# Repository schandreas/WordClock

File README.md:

# WordClock
WordClock based on a cheap stm32 chip (STM32F030RCT6TR)

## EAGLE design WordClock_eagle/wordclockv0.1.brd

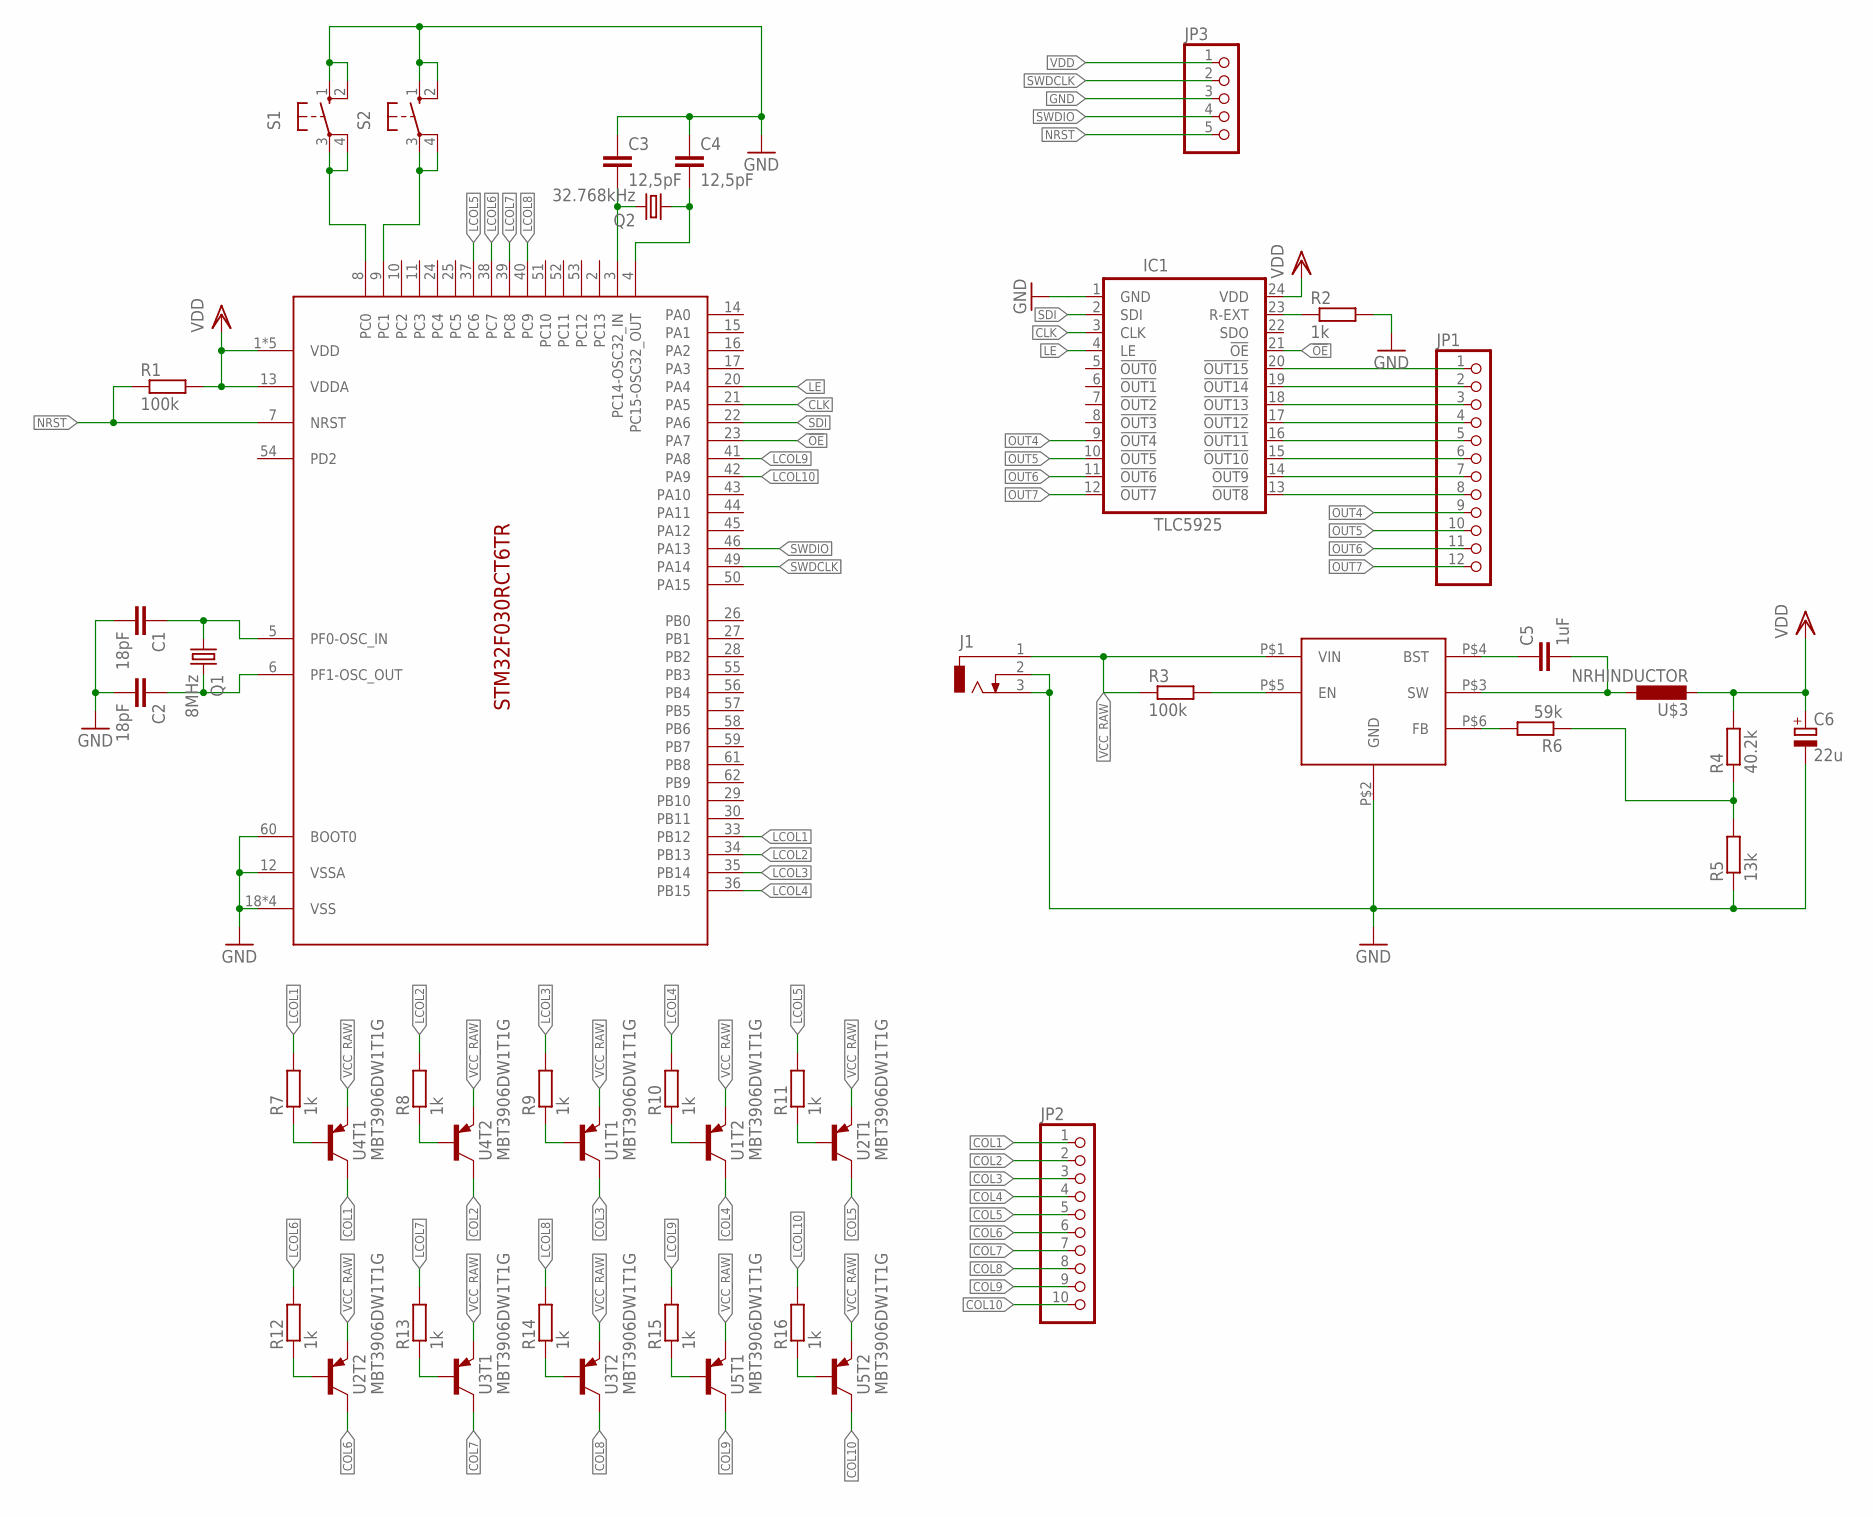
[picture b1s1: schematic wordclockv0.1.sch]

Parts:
C1, C2: 18pF; C0402
C3, C4: 12,5pF; C0402
C5: 1uF; C0805
C6: 22u; 153CLV-0405
IC1: TLC5925; SO24W
J1: DCJ0303
JP1: PINHD-1X12; 1X12
JP2: PINHD-1X10; 1X10
JP3: PINHD-1X5; 1X05
Q1: 8MHz; HC49U-V
Q2: 32.768kHz; TC26V
R1, R3: 100k; M1206
R2, R7, R8, R9, R10, R11, R12, R13, R14, R15, R16: 1k; M1206
R4: 40.2k; M1206
R5: 13k; M1206
R6: 59k; M1206
S1, S2: 10-XX; B3F-10XX
U1, U2, U3, U4, U5: MBT3906DW1T1G; SOT363-INFINION
U$1: STM32F030RCT6TRLQFP64; LQFP64
U$2: AP65111A; TSOT26
U$3: NRHINDUCTOR

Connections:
!OE: IC1.21 (!OE), U$1.23 (PA7)
CLK: IC1.3 (CLK), U$1.21 (PA5)
COL1: JP2.1, U4.6 (C)
COL2: JP2.2, U4.3 (C)
COL3: JP2.3, U1.6 (C)
COL4: JP2.4, U1.3 (C)
COL5: JP2.5, U2.6 (C)
COL6: JP2.6, U2.3 (C)
COL7: JP2.7, U3.6 (C)
COL8: JP2.8, U3.3 (C)
COL9: JP2.9, U5.6 (C)
COL10: JP2.10, U5.3 (C)
GND: C1.2, C2.2, C3.1, C4.1, C6.-, IC1.1 (GND), J1.2, J1.3, JP3.3, R2.2, R5.1, S1.1 (S), S1.2 (S1), S2.1 (S), S2.2 (S1), U$1.12 (VSSA), U$1.18 (VSS), U$1.31 (VSS), U$1.47 (VSS), U$1.60 (BOOT0), U$1.63 (VSS), U$2.P$2 (GND)
LCOL1: R7.2, U$1.33 (PB12)
LCOL2: R8.2, U$1.34 (PB13)
LCOL3: R9.2, U$1.35 (PB14)
LCOL4: R10.2, U$1.36 (PB15)
LCOL5: R11.2, U$1.37 (PC6)
LCOL6: R12.2, U$1.38 (PC7)
LCOL7: R13.2, U$1.39 (PC8)
LCOL8: R14.2, U$1.40 (PC9)
LCOL9: R15.2, U$1.41 (PA8)
LCOL10: R16.2, U$1.42 (PA9)
LE: IC1.4 (LE), U$1.20 (PA4)
unnamed: C1.1, Q1.1, U$1.5 (PF0-OSC_IN)
unnamed: C2.1, Q1.2, U$1.6 (PF1-OSC_OUT)
unnamed: C4.2, Q2.1, U$1.4 (PC15-OSC32_OUT)
unnamed: C3.2, Q2.2, U$1.3 (PC14-OSC32_IN)
unnamed: C5.1, U$2.P$4 (BST)
unnamed: R3.2, U$2.P$5 (EN)
unnamed: IC1.23 (R-EXT), R2.1
unnamed: C5.2, U$2.P$3 (SW), U$3.P$1 (1)
unnamed: R6.2, U$2.P$6 (FB)
unnamed: R4.1, R5.2, R6.1
unnamed: R7.1, U4.2 (B)
unnamed: R8.1, U4.5 (B)
unnamed: S1.3, S1.4 (P1), U$1.8 (PC0)
unnamed: R9.1, U1.2 (B)
unnamed: R10.1, U1.5 (B)
unnamed: S2.3, S2.4 (P1), U$1.9 (PC1)
unnamed: R11.1, U2.2 (B)
unnamed: R12.1, U2.5 (B)
unnamed: IC1.20 (!OUT15), JP1.1
unnamed: IC1.19 (!OUT14), JP1.2
unnamed: IC1.18 (!OUT13), JP1.3
unnamed: IC1.17 (!OUT12), JP1.4
unnamed: IC1.16 (!OUT11), JP1.5
unnamed: IC1.15 (!OUT10), JP1.6
unnamed: IC1.14 (!OUT9), JP1.7
unnamed: IC1.13 (!OUT8), JP1.8
unnamed: R13.1, U3.2 (B)
unnamed: R14.1, U3.5 (B)
unnamed: R15.1, U5.2 (B)
unnamed: R16.1, U5.5 (B)
NRST: JP3.5, R1.1, U$1.7 (NRST)
OUT4: IC1.9 (!OUT4), JP1.9
OUT5: IC1.10 (!OUT5), JP1.10
OUT6: IC1.11 (!OUT6), JP1.11
OUT7: IC1.12 (!OUT7), JP1.12
SDI: IC1.2 (SDI), U$1.22 (PA6)
SWDCLK: JP3.2, U$1.49 (PA14)
SWDIO: JP3.4, U$1.46 (PA13)
VCC_RAW: J1.1, R3.1, U1.1 (E), U1.4 (E), U2.1 (E), U2.4 (E), U3.1 (E), U3.4 (E), U4.1 (E), U4.4 (E), U5.1 (E), U5.4 (E), U$2.P$1 (VIN)
VDD: C6.+, IC1.24 (VDD), JP3.1, R1.2, R4.2, U$1.1 (VDD), U$1.13 (VDDA), U$1.19 (VDD), U$1.32 (VDD), U$1.48 (VDD), U$1.64 (VDD), U$3.P$2 (2)

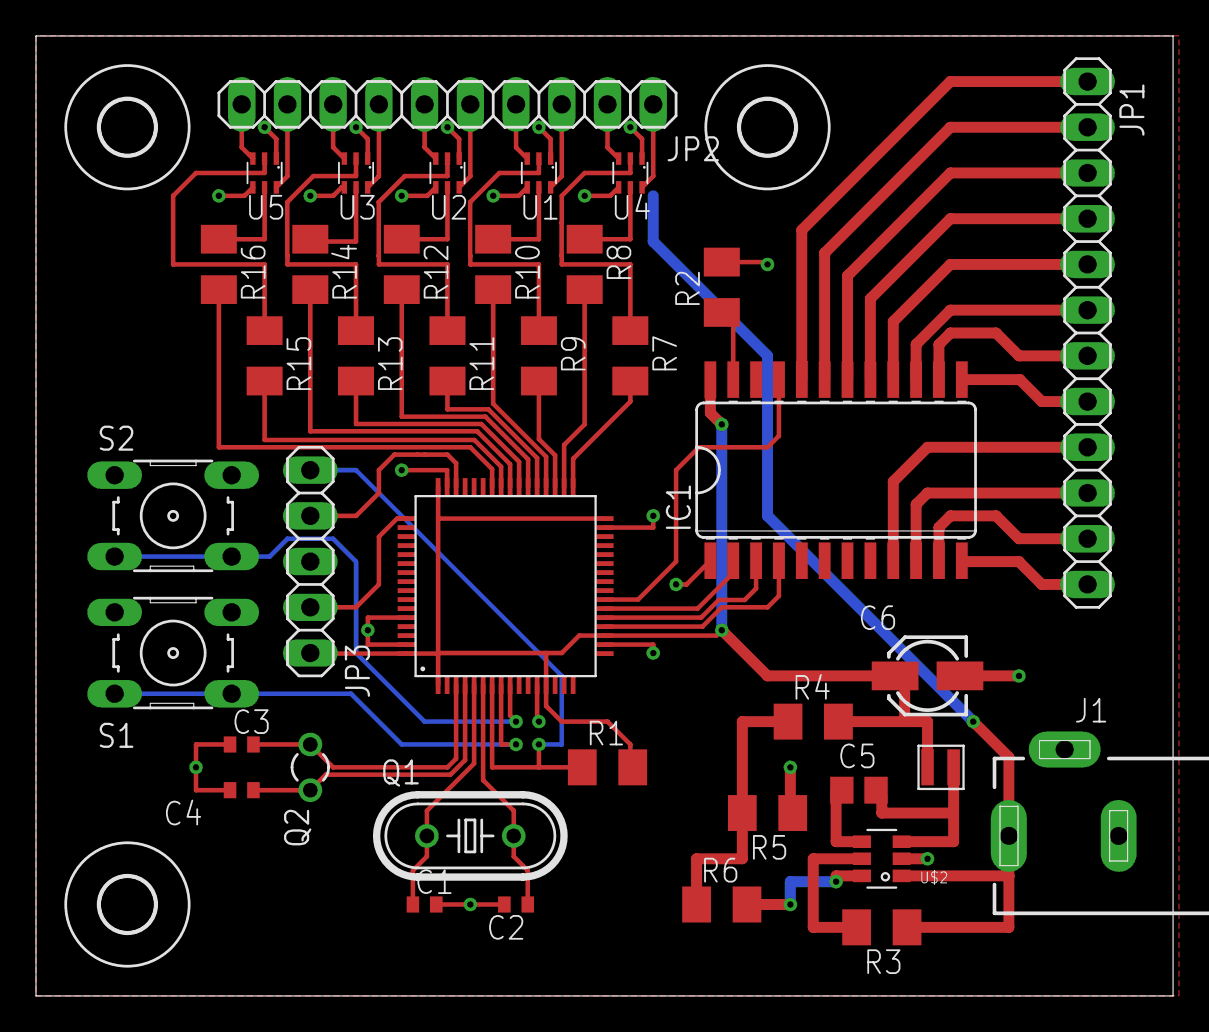
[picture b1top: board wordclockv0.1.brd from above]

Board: 2 copper layers, 63.2 x 53.3 mm, 42 parts (0 on the bottom side), 64 nets.

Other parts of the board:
U$4, U$5, U$6: 3,0

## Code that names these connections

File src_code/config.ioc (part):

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Mcu.Name=STM32F030RCTx
Mcu.Package=LQFP64
Mcu.UserName=STM32F030RCTx
PA13.Mode=Serial_Wire
PA13.Signal=SYS_SWDIO
PA14.Mode=Serial_Wire
PA14.Signal=SYS_SWCLK
PA4.GPIOParameters=GPIO_Label
PA4.GPIO_Label=LE
PA4.Signal=GPIO_Output
PA5.GPIOParameters=GPIO_Label
PA5.GPIO_Label=CLK
PA5.Signal=GPIO_Output
PA6.GPIOParameters=GPIO_Label
PA6.GPIO_Label=SDI
PA6.Signal=GPIO_Output
PA7.GPIOParameters=GPIO_Label
PA7.GPIO_Label=OE
PA7.Signal=GPIO_Output
PA8.GPIOParameters=GPIO_Label
PA8.GPIO_Label=LCOL9
PA8.Signal=GPIO_Output
PA9.GPIOParameters=GPIO_Label
PA9.GPIO_Label=LCOL10
PA9.Signal=GPIO_Output
PB12.GPIOParameters=GPIO_Label
PB12.GPIO_Label=LCOL1
PB12.Signal=GPIO_Output
PB13.GPIOParameters=GPIO_Label
PB13.GPIO_Label=LCOL2
PB13.Signal=GPIO_Output
PB14.GPIOParameters=GPIO_Label
PB14.GPIO_Label=LCOL3
PB14.Signal=GPIO_Output
PB15.GPIOParameters=GPIO_Label
PB15.GPIO_Label=LCOL4
PB15.Signal=GPIO_Output
PC0.GPIOParameters=GPIO_Label
PC0.GPIO_Label=BTN1
PC0.Signal=GPIO_Input
PC1.GPIOParameters=GPIO_Label
PC1.GPIO_Label=BTN2
PC1.Signal=GPIO_Input
PC14OSC32_IN.Mode=LSE-External-Oscillator
PC14OSC32_IN.Signal=RCC_OSC32_IN
PC15OSC32_OUT.Mode=LSE-External-Oscillator
PC15OSC32_OUT.Signal=RCC_OSC32_OUT
PC6.GPIOParameters=GPIO_Label
PC6.GPIO_Label=LCOL5
PC6.Signal=GPIO_Output
PC7.GPIOParameters=GPIO_Label
PC7.GPIO_Label=LCOL6
PC7.Signal=GPIO_Output
PC8.GPIOParameters=GPIO_Label
PC8.GPIO_Label=LCOL7
PC8.Signal=GPIO_Output
PC9.GPIOParameters=GPIO_Label
PC9.GPIO_Label=LCOL8
PC9.Signal=GPIO_Output
PF0-OSC_IN.Mode=HSE-External-Oscillator
PF0-OSC_IN.Signal=RCC_OSC_IN
PF1-OSC_OUT.Mode=HSE-External-Oscillator
PF1-OSC_OUT.Signal=RCC_OSC_OUT
RCC.SYSCLKFreq_VALUE=40000000
RCC.SYSCLKSource=RCC_SYSCLKSOURCE_PLLCLK
board=custom

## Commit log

2018-09-26 Added everything there is so far
2018-09-26 Changed the description to match whats actually in the lbr. Also gave credit
2018-09-26 Corrected spelling error. Worked on schematic.
    Spelling was bugging me. Had to get this out:disappointed_relieved:
2018-09-26 Changed the crystal
2018-09-27 Started the board. Still a lot of problems. not finished
2018-09-27 schematic changes. deleted brd
    board was deleted because i added a switching regulator and i'd need to rework the whole thing anyway. no point in keeping it. :imp:
2018-09-27 schematic changes. deleted brd. lbr changes
    board was deleted because i added a switching regulator and i'd need to rework the whole thing anyway. no point in keeping it. :imp:
    I also added devices for the regulator and the inductor i need to the lbr.
2018-09-27 Finished schematic for now. Starting on board
2018-09-28 Did the board. Rough draft without consideration for manufacturing
    Fabricating this thing is going to be hell :imp:
2018-09-28 Added cam file for manufacturing
    noone screamed at me yet
2018-09-28 Made a parts list from digikey. Changed some components bc cheaper
    Whoa this was a piece of work.
2018-10-03 Small changes to schematic and pcb
2018-10-03 Removed wire stubs from board. Also added .cam file for generating jlcpcb
2018-10-17 Leds are now fed by VCC_RAW instead of 3V3
2018-10-24 Updated the cam file for jlcpcb. The other files are just minor changes
    idk bro seems pretty sketchy
2018-10-27 Added config for STM32CubeMX. This starts the software side of things
    Dear god help me i am such an idiot at programming these things. If you think you can improve upon my shitty excuse for code you are welcome to submit a pull request. Every little thing helps
2018-10-27 Added just the generated project. Nothing more bc no hardware yet.
    I mean it's something right? right?
2018-10-29 Removed redundant .ioc file. Added Part numbers for farnell
2018-11-07 Added CAD File for German Front panel.
    Made by Sandra D.
    She didn't want to give me her twitter. go shout at her instead
2018-11-16 Did some groundwork on the code.
    Scream at me all you want the code is staying this bad.
2018-11-17 Finished the first version that hopefully (?) works
    Honestly this thing is probably filled to the brim with bugs but I don't have the hardware yet. Monday should be the frist day of actual testing
2018-11-28 Fixing huge error with stm32 pinout. Also revising board
    My package was numbered differently than the diagram in the datasheet. Didn't realize until the thing was hot to the touch and not responding. sucks to be me
